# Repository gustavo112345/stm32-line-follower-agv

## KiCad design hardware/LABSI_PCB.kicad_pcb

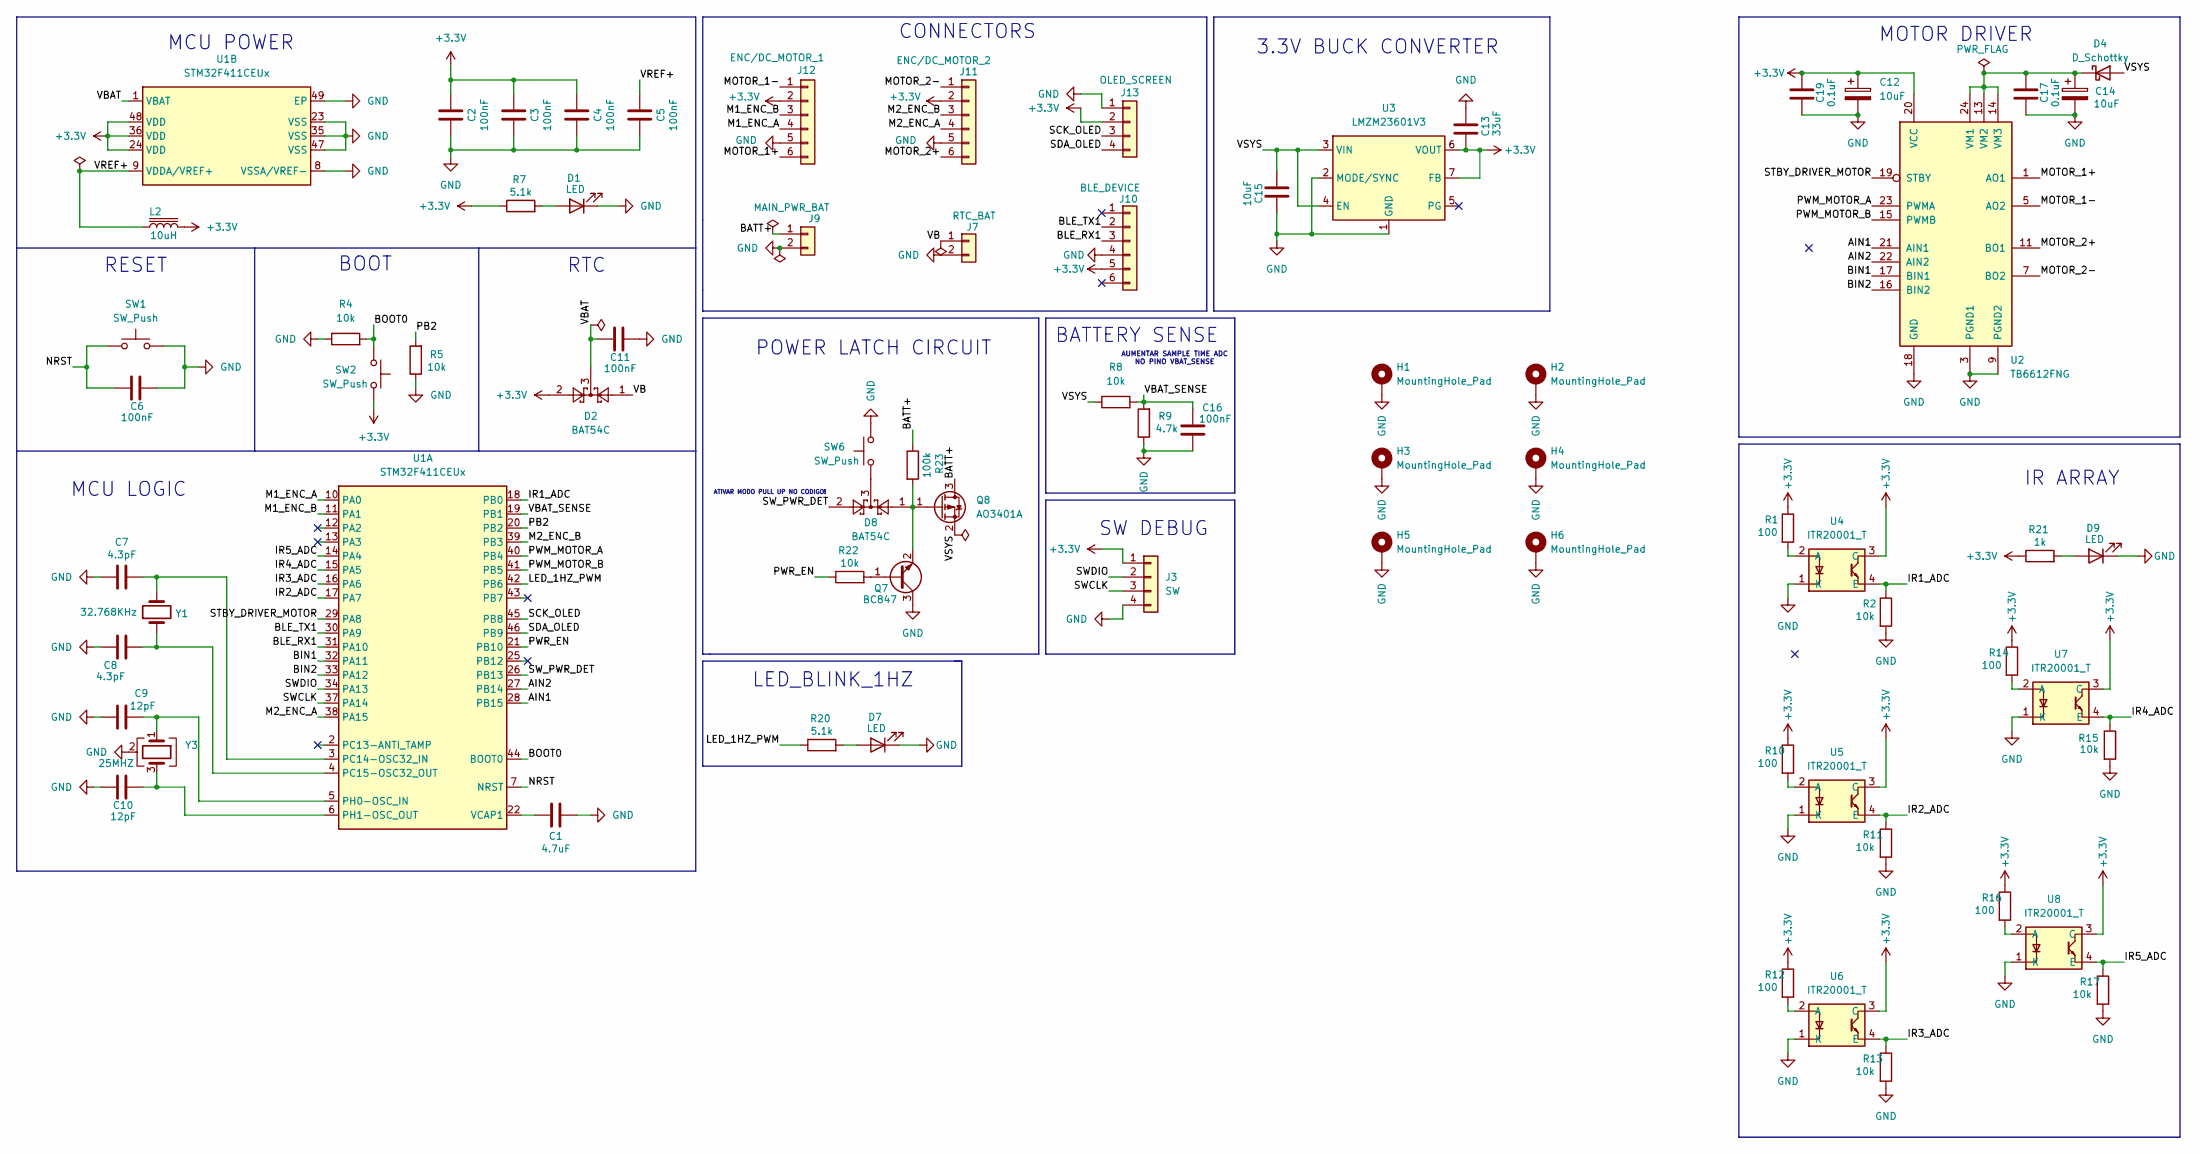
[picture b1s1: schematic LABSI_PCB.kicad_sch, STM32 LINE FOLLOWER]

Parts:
C1: 4.7uF; C_0603_1608Metric
C2, C3, C4, C5, C6, C11, C16: 100nF; C_0603_1608Metric
C7, C8: 4.3pF; C_0603_1608Metric
C9, C10: 12pF; C_0603_1608Metric
C12, C14: 10uF; CP_EIA-3216-18_Kemet-A
C13: 33uF; C_0603_1608Metric
C15: 10uF; C_0603_1608Metric
C17, C19: 0.1uF; C_0603_1608Metric
D1, D7, D9: LED; LED_0805_2012Metric
D2, D8: BAT54C; SOT-23
D4: D_Schottky; D_SMA
H1, H2, H3, H4: MountingHole_Pad; MountingHole_2.2mm_M2_Pad_TopBottom
H5, H6: MountingHole_Pad; MountingHole_3.2mm_M3_Pad_TopBottom
J3: SW; PinHeader_1x04_P2.54mm_Vertical
J7: RTC_BAT; BatteryHolder_Keystone_1058_1x2032
J9: MAIN_PWR_BAT; JST_EH_B2B-EH-A_1x02_P2.50mm_Vertical
J10: BLE_DEVICE; PinSocket_1x06_P2.54mm_Vertical
J11: ENC/DC_MOTOR_2; JST_ZH_B6B-ZR_1x06_P1.50mm_Vertical
J12: ENC/DC_MOTOR_1; JST_ZH_B6B-ZR_1x06_P1.50mm_Vertical
J13: OLED_SCREEN; PinSocket_1x04_P2.54mm_Vertical
L2: 10uH; L_0805_2012Metric
Q7: BC847; SOT-23
Q8: AO3401A; SOT-23
R1, R10, R12, R14, R16: 100; R_0603_1608Metric
R2, R4, R5, R8, R11, R13, R15, R17, R22: 10k; R_0603_1608Metric
R7, R20: 5.1k; R_0603_1608Metric
R9: 4.7k; R_0603_1608Metric
R21: 1k; R_0603_1608Metric
R23: 100k; R_0603_1608Metric
SW1, SW2, SW6: SW_Push; SW_SPST_B3U-1000P
U1: STM32F411CEUx; QFN-48-1EP_7x7mm_P0.5mm_EP5.6x5.6mm
U2: TB6612FNG; SSOP-24_5.3x8.2mm_P0.65mm
U3: LMZM23601V3; Texas_SIL0010A_MicroSiP-10-1EP_3.8x3mm_P0.6mm_EP0.7x2.9mm_T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
U4, U5, U6, U7, U8: ITR20001_T; RELAY4_ITR20001_T_EVE; Manufacturer_Part_Number ITR20001/T
Y1: 32.768KHz; Crystal_SMD_3215-2Pin_3.2x1.5mm
Y3: 25MHZ; Crystal_SMD_3225-4Pin_3.2x2.5mm

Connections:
+3.3V: C2.1, C3.1, C4.1, C12.1, C13.2, C19.2, D2.2, J3.1, J10.5, J11.2, J12.2, J13.2, L2.2, R1.1, R7.1, R10.1, R12.1, R14.1, R16.1, R21.1, SW2.2, U1.24 (VDD), U1.36 (VDD), U1.48 (VDD), U2.20 (VCC), U3.6 (VOUT), U3.7 (FB), U4.3 (C), U5.3 (C), U6.3 (C), U7.3 (C), U8.3 (C)
/AIN1: U1.28 (PB15), U2.21 (AIN1)
/AIN2: U1.27 (PB14), U2.22 (AIN2)
/BATT+: J9.1, Q8.3 (D), R23.1
/BIN1: U1.32 (PA11), U2.17 (BIN1)
/BIN2: U1.33 (PA12), U2.16 (BIN2)
/BLE_RX1: J10.3, U1.31 (PA10)
/BLE_TX1: J10.2, U1.30 (PA9)
/BOOT0: R4.2, SW2.1, U1.44 (BOOT0)
/IR1_ADC: R2.1, U1.18 (PB0), U4.4 (E)
/IR2_ADC: R11.1, U1.17 (PA7), U5.4 (E)
/IR3_ADC: R13.1, U1.16 (PA6), U6.4 (E)
/IR4_ADC: R15.1, U1.15 (PA5), U7.4 (E)
/IR5_ADC: R17.1, U1.14 (PA4), U8.4 (E)
/LED_1HZ_PWM: R20.1, U1.42 (PB6)
/M1_ENC_A: J12.4, U1.10 (PA0)
/M1_ENC_B: J12.3, U1.11 (PA1)
/M2_ENC_A: J11.4, U1.38 (PA15)
/M2_ENC_B: J11.3, U1.39 (PB3)
/MOTOR_1+: J12.6, U2.1 (AO1), U2.2 (AO1)
/MOTOR_1-: J12.1, U2.5 (AO2), U2.6 (AO2)
/MOTOR_2+: J11.6, U2.11 (BO1), U2.12 (BO1)
/MOTOR_2-: J11.1, U2.7 (BO2), U2.8 (BO2)
/NRST: C6.1, SW1.1, U1.7 (NRST)
/PB2: R5.2, U1.20 (PB2)
/PWM_MOTOR_A: U1.40 (PB4), U2.23 (PWMA)
/PWM_MOTOR_B: U1.41 (PB5), U2.15 (PWMB)
/PWR_EN: R22.1, U1.21 (PB10)
/SCK_OLED: J13.3, U1.45 (PB8)
/SDA_OLED: J13.4, U1.46 (PB9)
/STBY_DRIVER_MOTOR: U1.29 (PA8), U2.19 (STBY)
/SWCLK: J3.3, U1.37 (PA14)
/SWDIO: J3.2, U1.34 (PA13)
/SW_PWR_DET: D8.2, U1.26 (PB13)
/VB: D2.1, J7.1
/VBAT: C11.1, D2.3, U1.1 (VBAT)
/VBAT_SENSE: C16.2, R8.2, R9.2, U1.19 (PB1)
/VREF+: C5.1, L2.1, U1.9 (VDDA/VREF+)
/VSYS: C15.1, D4.2 (A), Q8.2 (S), R8.1, U3.3 (VIN), U3.4 (EN)
GND: C1.1, C2.2, C3.2, C4.2, C5.2, C6.2, C7.1, C8.1, C9.1, C10.1, C11.2, C12.2, C13.1, C14.2, C15.2, C16.1, C17.1, C19.1, D1.1 (K), D7.1 (K), D9.1 (K), H1.1 (1_1), H2.1 (1_1), H3.1 (1_1), H4.1 (1_1), H5.1 (1_1), H6.1 (1_1), J3.4, J7.2, J9.2, J10.4, J11.5, J12.5, J13.1, Q7.3 (C), R2.2, R4.1, R5.1, R9.1, R11.2, R13.2, R15.2, R17.2, SW1.2, SW6.2, U1.8 (VSSA/VREF-), U1.23 (VSS), U1.35 (VSS), U1.47 (VSS), U1.49 (EP), U2.3 (PGND1), U2.4 (PGND1), U2.9 (PGND2), U2.10 (PGND2), U2.18 (GND), U3.1 (GND), U3.2 (MODE/SYNC), U3.11 (GND), U4.1 (K), U5.1 (K), U6.1 (K), U7.1 (K), U8.1 (K), Y3.2 (G), Y3.4 (G)
unnamed: D1.2 (A), R7.2
unnamed: C14.1, C17.2, D4.1 (K), U2.13 (VM2), U2.14 (VM3), U2.24 (VM1)
unnamed: D7.2 (A), R20.2
unnamed: D8.3, SW6.1
unnamed: D9.2 (A), R21.2
unnamed: Q7.1 (B), R22.2
unnamed: D8.1, Q7.2 (E), Q8.1 (G), R23.2
unnamed: C7.2, U1.3 (PC14-OSC32_IN), Y1.2
unnamed: C8.2, U1.4 (PC15-OSC32_OUT), Y1.1
unnamed: C9.2, U1.5 (PH0-OSC_IN), Y3.1
unnamed: C10.2, U1.6 (PH1-OSC_OUT), Y3.3
unnamed: C1.2, U1.22 (VCAP1)
unnamed: R1.2, U4.2 (A)
unnamed: R10.2, U5.2 (A)
unnamed: R12.2, U6.2 (A)
unnamed: R14.2, U7.2 (A)
unnamed: R16.2, U8.2 (A)

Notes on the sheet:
LED_BLINK_1HZ
POWER LATCH CIRCUIT
RTC
RESET
3.3V BUCK CONVERTER
MCU LOGIC
CONNECTORS
BOOT
AUMENTAR SAMPLE TIME ADC NO PINO VBAT_SENSE
ATIVAR MODO PULL UP NO CODIGO!
IR ARRAY
SW DEBUG
BATTERY SENSE
MCU POWER
MOTOR DRIVER

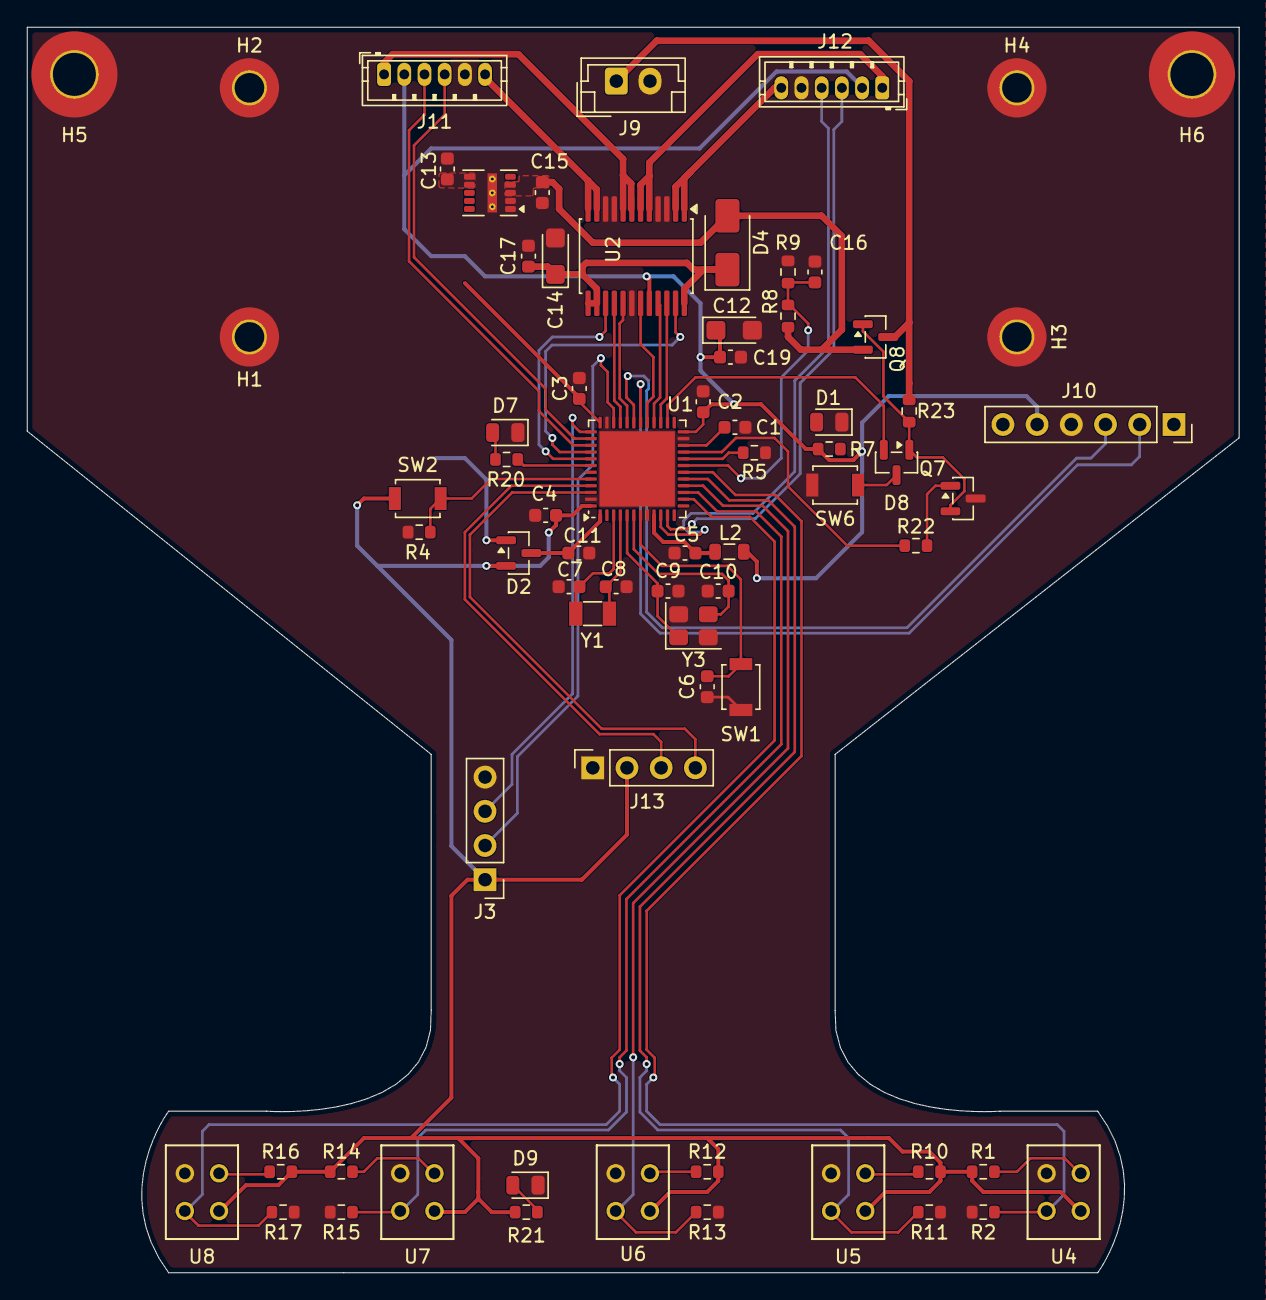
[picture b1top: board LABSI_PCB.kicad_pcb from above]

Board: 4 copper layers, 90.0 x 92.5 mm, 72 parts (1 on the bottom side), 57 nets.

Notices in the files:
parts and their libraries:
Copyright: Copyright (C) 2022 Ultra Librarian. All rights reserved.
